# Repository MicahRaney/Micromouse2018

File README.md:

View this project on [CADLAB.io](https://cadlab.io/project/1563). 

# Micromouse2018

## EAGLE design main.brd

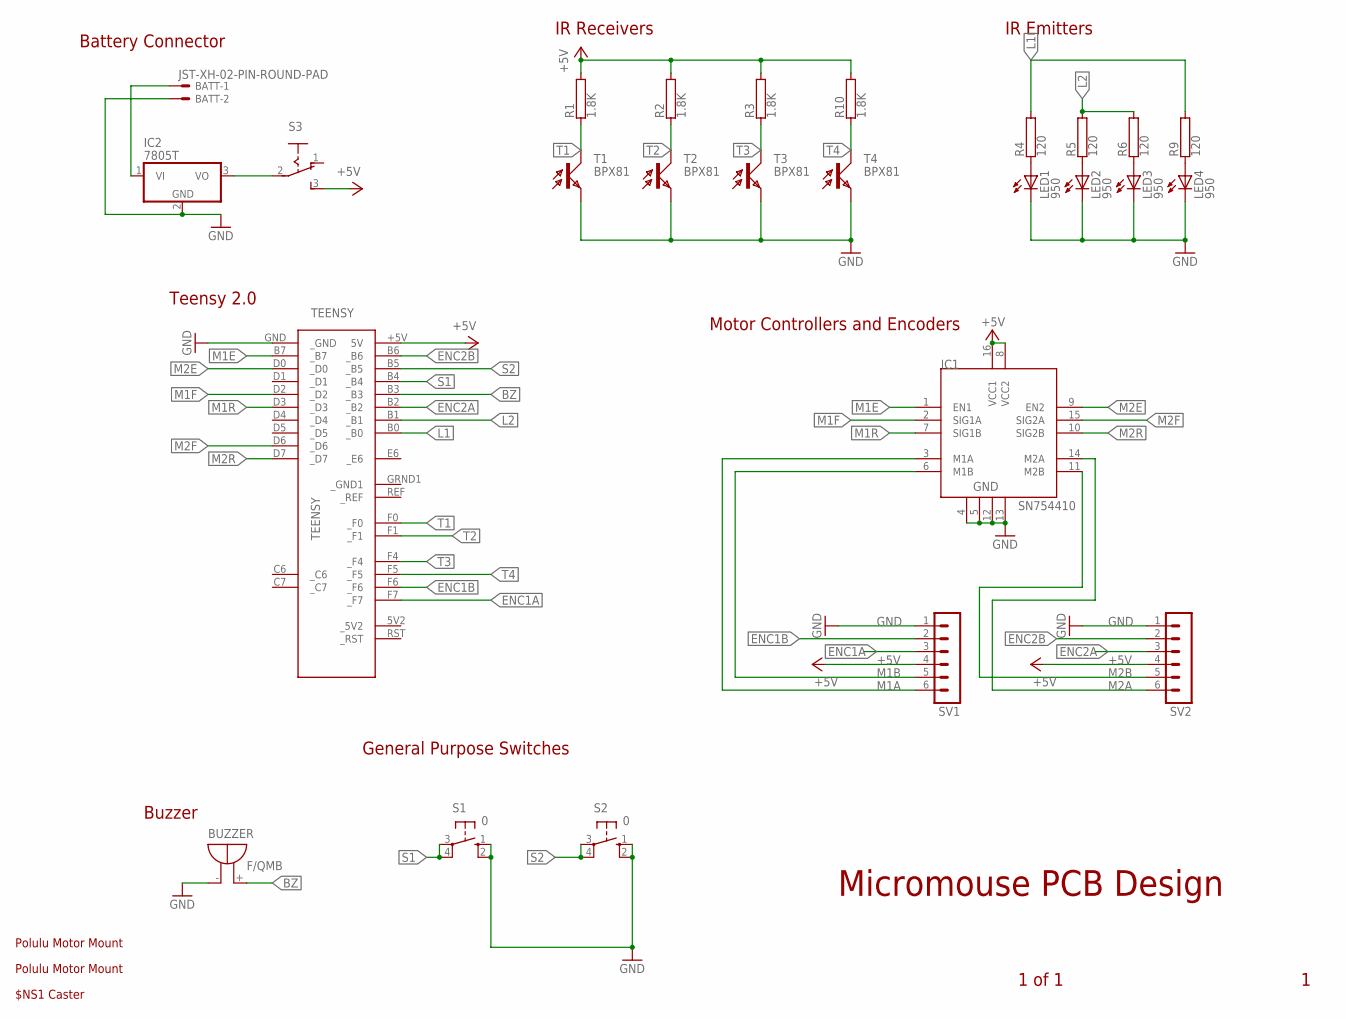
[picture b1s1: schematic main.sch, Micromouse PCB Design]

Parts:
BATT: JST-XH-02-PIN-ROUND-PAD; JST-XH-02-PACKAGE-ROUND-PAD
BUZZER: F/QMB
IC1: SN754410; DIP16; MPN SN754410NE
IC2: 7805T; TO220H; MPN NCP7805TG
LED1, LED2, LED3, LED4: 950; LED3MM; MPN CNX_B_E_4_1_04
R1, R2, R3, R10: 1.8K; RS1/4
R4, R5, R6, R9: 120; RS1/4
S1, S2: 0; B3F-10XX
S3: 255SB
SV1, SV2: MA06-1
T1, T2, T3, T4: BPX81
TEENSY: TEENSY
U$1, U$2: POLULUMOTOR; FP
U$3: CASTERBALL; FB_CASTER

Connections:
+5V: IC1.8 (VCC2), IC1.16 (VCC1), R1.2, R2.2, R3.2, R10.2, S3.3 (S), SV1.4, SV2.4, TEENSY.+5V (5V)
BZ: BUZZER.+ (-), TEENSY.B3 (_B3)
ENC1A: SV1.3, TEENSY.F7 (_F7)
ENC1B: SV1.2, TEENSY.F6 (_F6)
ENC2A: SV2.3, TEENSY.B2 (_B2)
ENC2B: SV2.2, TEENSY.B6 (_B6)
GND: BATT.2, BUZZER.- (+), IC1.4, IC1.5, IC1.12, IC1.13, IC2.2 (GND), LED1.K (C), LED2.K (C), LED3.K (C), LED4.K (C), S1.1 (S), S1.2 (S1), S2.1 (S), S2.2 (S1), SV1.1, SV2.1, T1.E, T2.E, T3.E, T4.E, TEENSY.GND (_GND)
L1: R4.2, R9.2, TEENSY.B0 (_B0)
L2: R5.2, R6.2, TEENSY.B1 (_B1)
M1A: IC1.3 (M1A), SV1.6
M1B: IC1.6 (M1B), SV1.5
M1E: IC1.1 (EN1), TEENSY.B7 (_B7)
M1F: IC1.2 (SIG1A), TEENSY.D2 (_D2)
M1R: IC1.7 (SIG1B), TEENSY.D3 (_D3)
M2A: IC1.14 (M2A), SV2.6
M2B: IC1.11 (M2B), SV2.5
M2E: IC1.9 (EN2), TEENSY.D0 (_D0)
M2F: IC1.15 (SIG2A), TEENSY.D6 (_D6)
M2R: IC1.10 (SIG2B), TEENSY.D7 (_D7)
unnamed: LED1.A, R4.1
unnamed: LED2.A, R5.1
unnamed: LED3.A, R6.1
unnamed: BATT.1, IC2.1 (VI)
unnamed: LED4.A, R9.1
unnamed: IC2.3 (VO), S3.2
S1: S1.3, S1.4 (P1), TEENSY.B4 (_B4)
S2: S2.3, S2.4 (P1), TEENSY.B5 (_B5)
T1: R1.1, T1.C, TEENSY.F0 (_F0)
T2: R2.1, T2.C, TEENSY.F1 (_F1)
T3: R3.1, T3.C, TEENSY.F4 (_F4)
T4: R10.1, T4.C, TEENSY.F5 (_F5)

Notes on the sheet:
General Purpose Switches
Buzzer
Motor Controllers and Encoders
IR Emitters
Battery Connector
Teensy 2.0
IR Receivers
1 of 1
Micromouse PCB Design

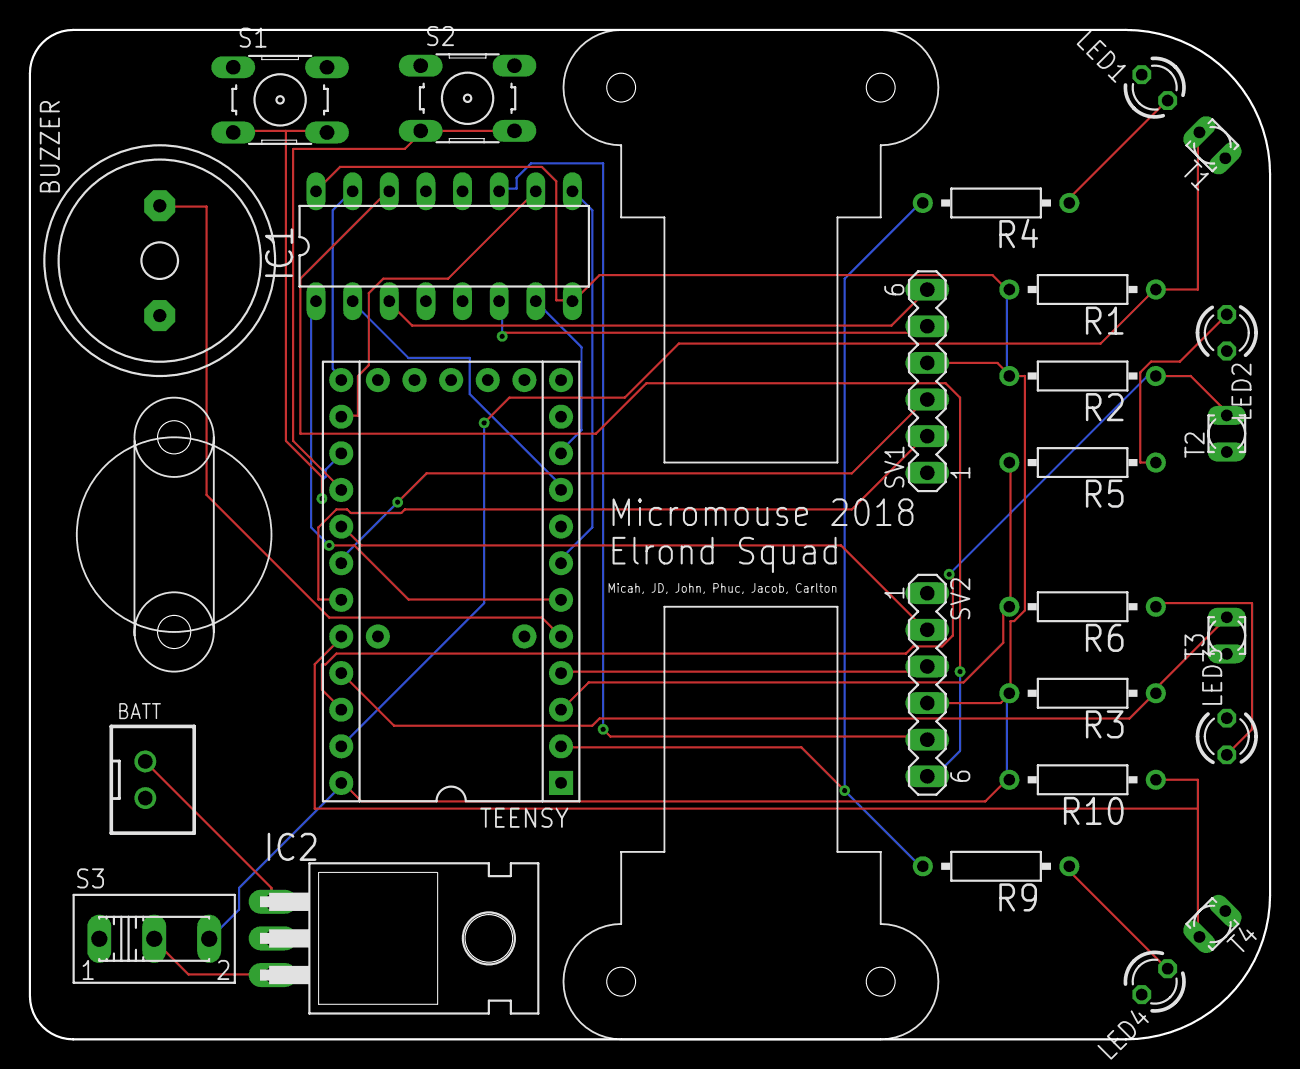
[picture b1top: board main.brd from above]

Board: 2 copper layers, 86.0 x 70.0 mm, 29 parts (0 on the bottom side), 31 nets.

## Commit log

2019-01-17 Backlink to CADLAB.io has been added.
2019-01-17 Added fourth LED/Emitter Combo and rerouted nets
2019-01-21 Changed Teensy 3.2 to Teensy 2.0
    Also changed switches to pull down on press, using pull up resistors on
    teensy.
2019-01-22 Made schematic and board consistent
    Also changed transistor package
2019-01-22 Laid out components on PCB
2019-02-21 Update motor connection and added power switch
2019-02-21 Removed gyroscope
2019-02-28 Updated motor
2019-02-28 Updated LED Wiring
2019-02-28 Peer Review Version
2019-02-28 Final artistic touches
2019-02-28 Added initial production request and layer changes
2019-02-28 Updated drill hole size and wiring
2019-03-11 Fixed broken nets on motor connectors
